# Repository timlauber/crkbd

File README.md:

# Corne keyboard

The Corne keyboard is a split keyboard with 3x6 column staggered keys
and 3 thumb keys, based on [Helix](https://github.com/MakotoKurauchi/helix).
Crkbd stands for Corne Keyboard.

## Lineup

- corne-chocolate:
  Hotswappable Corne for Chocolate switches using Kailh PCB hot-swap sockets.

## Photos

coming soon...

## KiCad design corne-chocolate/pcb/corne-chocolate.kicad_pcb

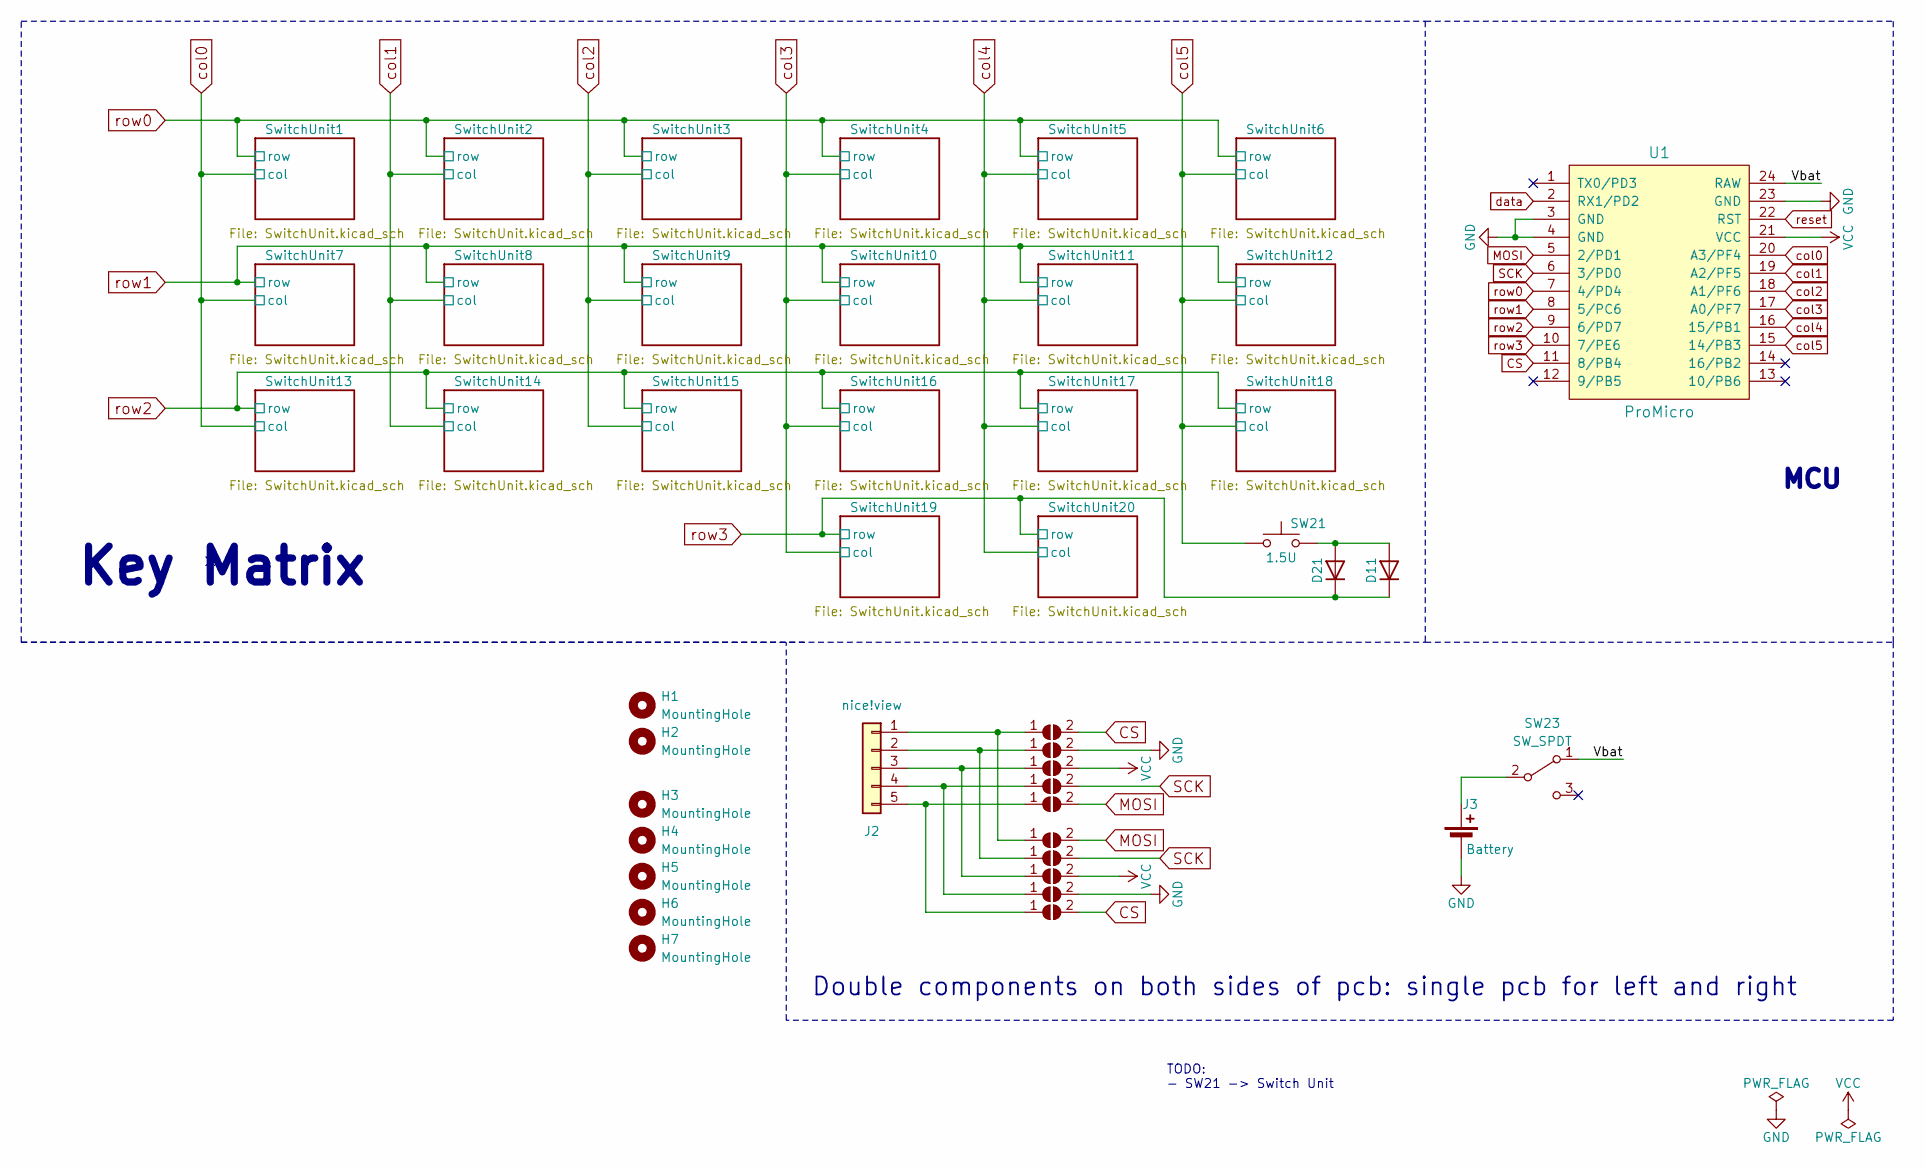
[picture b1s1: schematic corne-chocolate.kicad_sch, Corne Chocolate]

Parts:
D11, D21: 1N4148; D_SOD-323_HandSoldering
H1, H2: MountingHole; MountingHole_2.2mm_M2
H3, H4, H5, H6, H7: MountingHole; MountingHole_4.3mm_M4
J2: nice!view; PinHeader_1x05_P2.54mm_Vertical_noSilk
J3: Battery; JST_PH_S2B-K_doublesided
JP2, JP3, JP4, JP5, JP6, JP7, JP8, JP9, JP10, JP11: SolderJumper_2_Open; SolderJumper-2_P1.3mm_Open_RoundedPad1.0x1.5mm_noSilk_noCou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
SW21: 1.5U; Choc_Hotswap_1.5u
SW23: SW_SPDT; ECE_ESP2010
U1: ProMicro; ProMicro_v2

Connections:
/Vbat: SW23.1 (A), U1.24 (RAW)
CS: JP2.2 (B), JP11.2 (B), U1.11 (8/PB4)
GND: J3.2 (-), JP3.2 (B), JP10.2 (B), U1.3 (GND), U1.4 (GND), U1.23 (GND)
MOSI: JP6.2 (B), JP7.2 (B), U1.5 (2/PD1)
unnamed: D11.2 (A), D21.2 (A), SW21.2
unnamed: J2.1, JP2.1 (A), JP7.1 (A)
unnamed: J2.2, JP3.1 (A), JP8.1 (A)
unnamed: J2.3, JP4.1 (A), JP9.1 (A)
unnamed: J2.4, JP5.1 (A), JP10.1 (A)
unnamed: J2.5, JP6.1 (A), JP11.1 (A)
unnamed: J3.1 (+), SW23.2 (B)
SCK: JP5.2 (B), JP8.2 (B), U1.6 (3/PD0)
VCC: JP4.2 (B), JP9.2 (B), U1.21 (VCC)
col0: U1.20 (A3/PF4); also elsewhere on the board
col1: U1.19 (A2/PF5); also elsewhere on the board
col2: U1.18 (A1/PF6); also elsewhere on the board
col3: U1.17 (A0/PF7); also elsewhere on the board
col4: U1.16 (15/PB1); also elsewhere on the board
col5: SW21.1, U1.15 (14/PB3); also elsewhere on the board
data: U1.2 (RX1/PD2)
reset: U1.22 (RST)
row0: U1.7 (4/PD4); also elsewhere on the board
row1: U1.8 (5/PC6); also elsewhere on the board
row2: U1.9 (6/PD7); also elsewhere on the board
row3: D11.1 (K), D21.1 (K), U1.10 (7/PE6); also elsewhere on the board

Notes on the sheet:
MCU
Double components on both sides of pcb: single pcb for left and right
Key Matrix
TODO: - SW21 -> Switch Unit

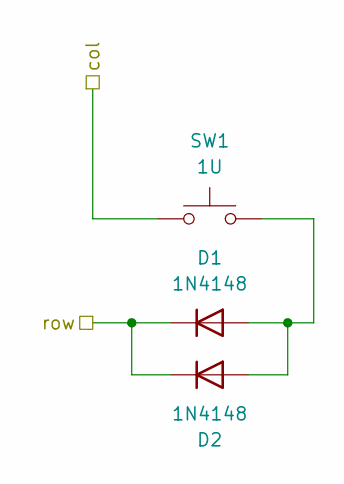
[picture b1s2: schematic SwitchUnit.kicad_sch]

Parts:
D1, D2: 1N4148; D_SOD-323_HandSoldering
SW1: 1U; Choc_Hotswap

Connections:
unnamed: D1.2 (A), D2.2 (A), SW1.2
col0: SW1.1; also elsewhere on the board
row0: D1.1 (K), D2.1 (K); also elsewhere on the board

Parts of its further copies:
D3, D4, D5, D6, D7, D8, D9, D10, D13, D14, D15, D22, D23, D24, D25, D26, D27, D28, D29, D30, D31, D32, D33, D34, D35, D36, D37, D38, D39, D40, D41, D42, D43, D44, D45, D46, D47, D48: 1N4148; D_SOD-323_HandSoldering
SW2, SW3, SW4, SW5, SW6, SW7, SW8, SW9, SW10, SW11, SW12, SW13, SW14, SW15, SW16, SW17, SW18, SW19, SW20: 1U; Choc_Hotswap

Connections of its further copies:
unnamed: D3.2 (A), D9.2 (A), SW4.2
unnamed: D4.2 (A), D5.2 (A), SW19.2
unnamed: D6.2 (A), D10.2 (A), SW20.2
unnamed: D8.2 (A), D13.2 (A), SW8.2
unnamed: D14.2 (A), D27.2 (A), SW14.2
unnamed: D15.2 (A), D34.2 (A), SW10.2
unnamed: D22.2 (A), D23.2 (A), SW2.2
unnamed: D24.2 (A), D25.2 (A), SW7.2
unnamed: D7.2 (A), D26.2 (A), SW13.2
unnamed: D28.2 (A), D29.2 (A), SW3.2
unnamed: D30.2 (A), D31.2 (A), SW9.2
unnamed: D32.2 (A), D33.2 (A), SW15.2
unnamed: D35.2 (A), D36.2 (A), SW16.2
unnamed: D37.2 (A), D38.2 (A), SW5.2
unnamed: D39.2 (A), D40.2 (A), SW11.2
unnamed: D41.2 (A), D42.2 (A), SW17.2
unnamed: D43.2 (A), D44.2 (A), SW6.2
unnamed: D45.2 (A), D46.2 (A), SW12.2
unnamed: D47.2 (A), D48.2 (A), SW18.2
col0: SW7.1, SW13.1; also elsewhere on the board
col1: SW2.1, SW8.1, SW14.1; also elsewhere on the board
col2: SW3.1, SW9.1, SW15.1; also elsewhere on the board
col3: SW4.1, SW10.1, SW16.1, SW19.1; also elsewhere on the board
col4: SW5.1, SW11.1, SW17.1, SW20.1; also elsewhere on the board
col5: SW6.1, SW12.1, SW18.1; also elsewhere on the board
row0: D3.1 (K), D9.1 (K), D22.1 (K), D23.1 (K), D28.1 (K), D29.1 (K), D37.1 (K), D38.1 (K), D43.1 (K), D44.1 (K); also elsewhere on the board
row1: D8.1 (K), D13.1 (K), D15.1 (K), D24.1 (K), D25.1 (K), D30.1 (K), D31.1 (K), D34.1 (K), D39.1 (K), D40.1 (K), D45.1 (K), D46.1 (K); also elsewhere on the board
row2: D7.1 (K), D14.1 (K), D26.1 (K), D27.1 (K), D32.1 (K), D33.1 (K), D35.1 (K), D36.1 (K), D41.1 (K), D42.1 (K), D47.1 (K), D48.1 (K); also elsewhere on the board
row3: D4.1 (K), D5.1 (K), D6.1 (K), D10.1 (K); also elsewhere on the board

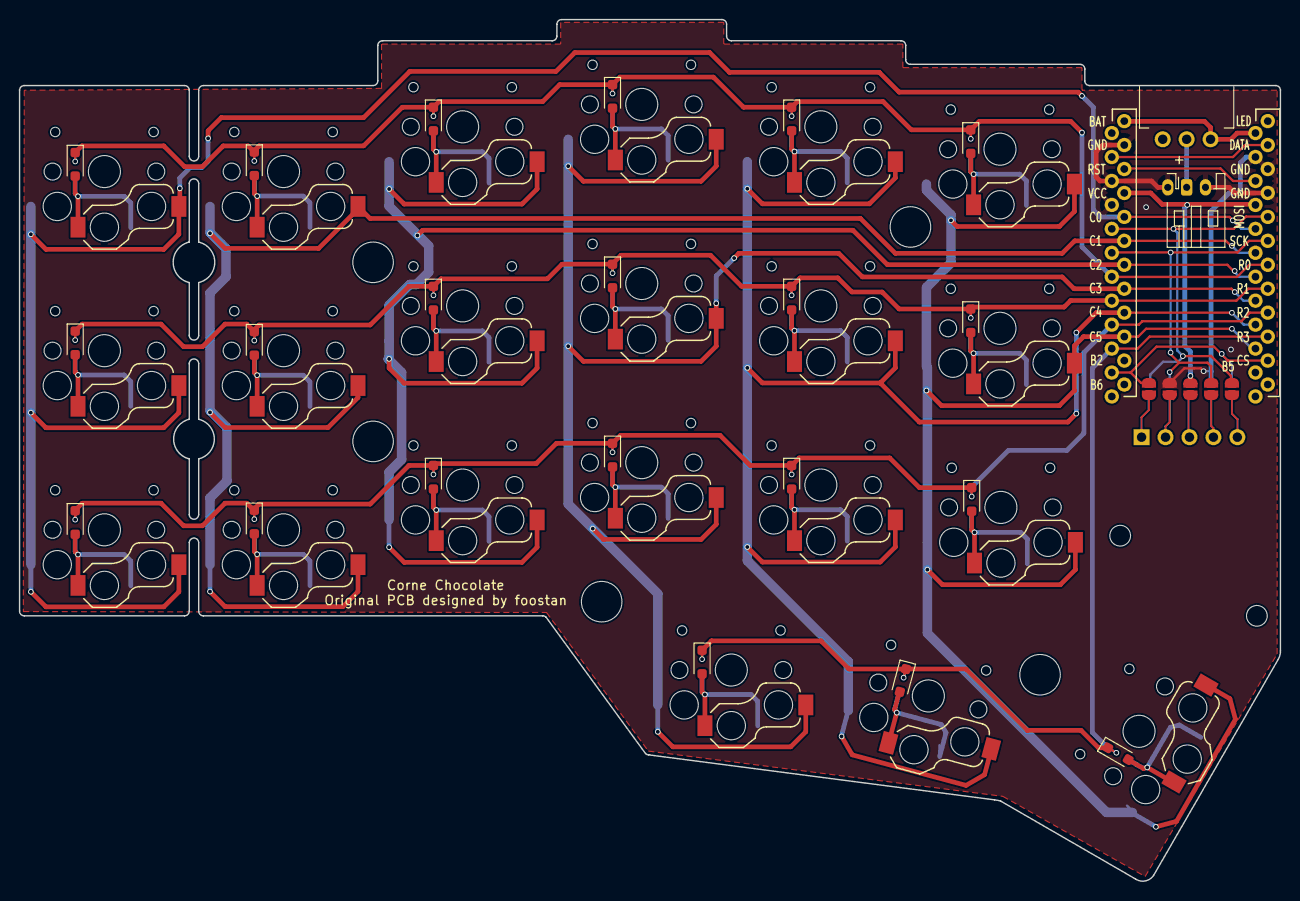
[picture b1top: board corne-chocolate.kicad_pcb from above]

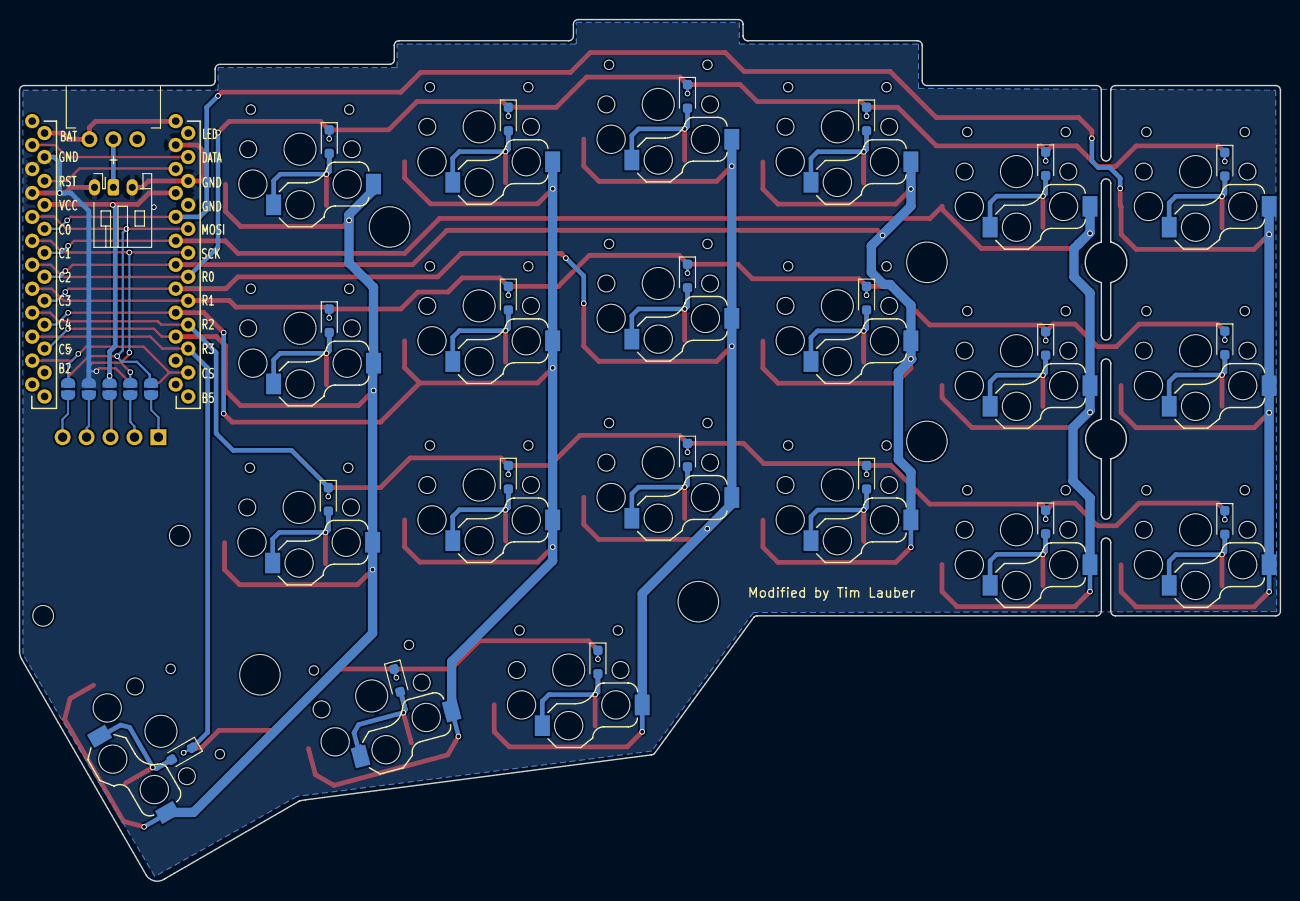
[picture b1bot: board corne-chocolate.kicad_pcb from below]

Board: 2 copper layers, 133.8 x 91.4 mm, 84 parts (27 on the bottom side), 43 nets.

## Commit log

2023-08-13 KiCAD7 support
2023-08-13 Cleanup schematic
2023-08-13 cleanup symbol library. copy symbols from pcb to new project specific library
2025-08-19 gitignore add *.log files
2025-08-19 corne-chocolate first modified version by timlauber: first cleanup of schematic and layout
2025-08-19 Clean slate
2025-08-19 pcb remove unused symbol libraries from symbol library table
2025-08-19 pcb layout -> KiCAD v9
2025-08-19 pcb change on/off switch
2025-08-19 pcb remove TRRS
2025-08-23 pcb clean up layout under MCU
2025-08-23 pcb remove underglow LEDs
2025-08-25 pcb remove per-switch LEDs
2025-08-25 pcb clean up mounting holes
2025-08-27 pcb replace SMD jumper with solder jumper
2025-08-31 pcb change corne logo to mask layer. Add my logo
2025-09-02 pcb add choc hotswap 3d model
2025-09-05 pcb change battery connector to THT
